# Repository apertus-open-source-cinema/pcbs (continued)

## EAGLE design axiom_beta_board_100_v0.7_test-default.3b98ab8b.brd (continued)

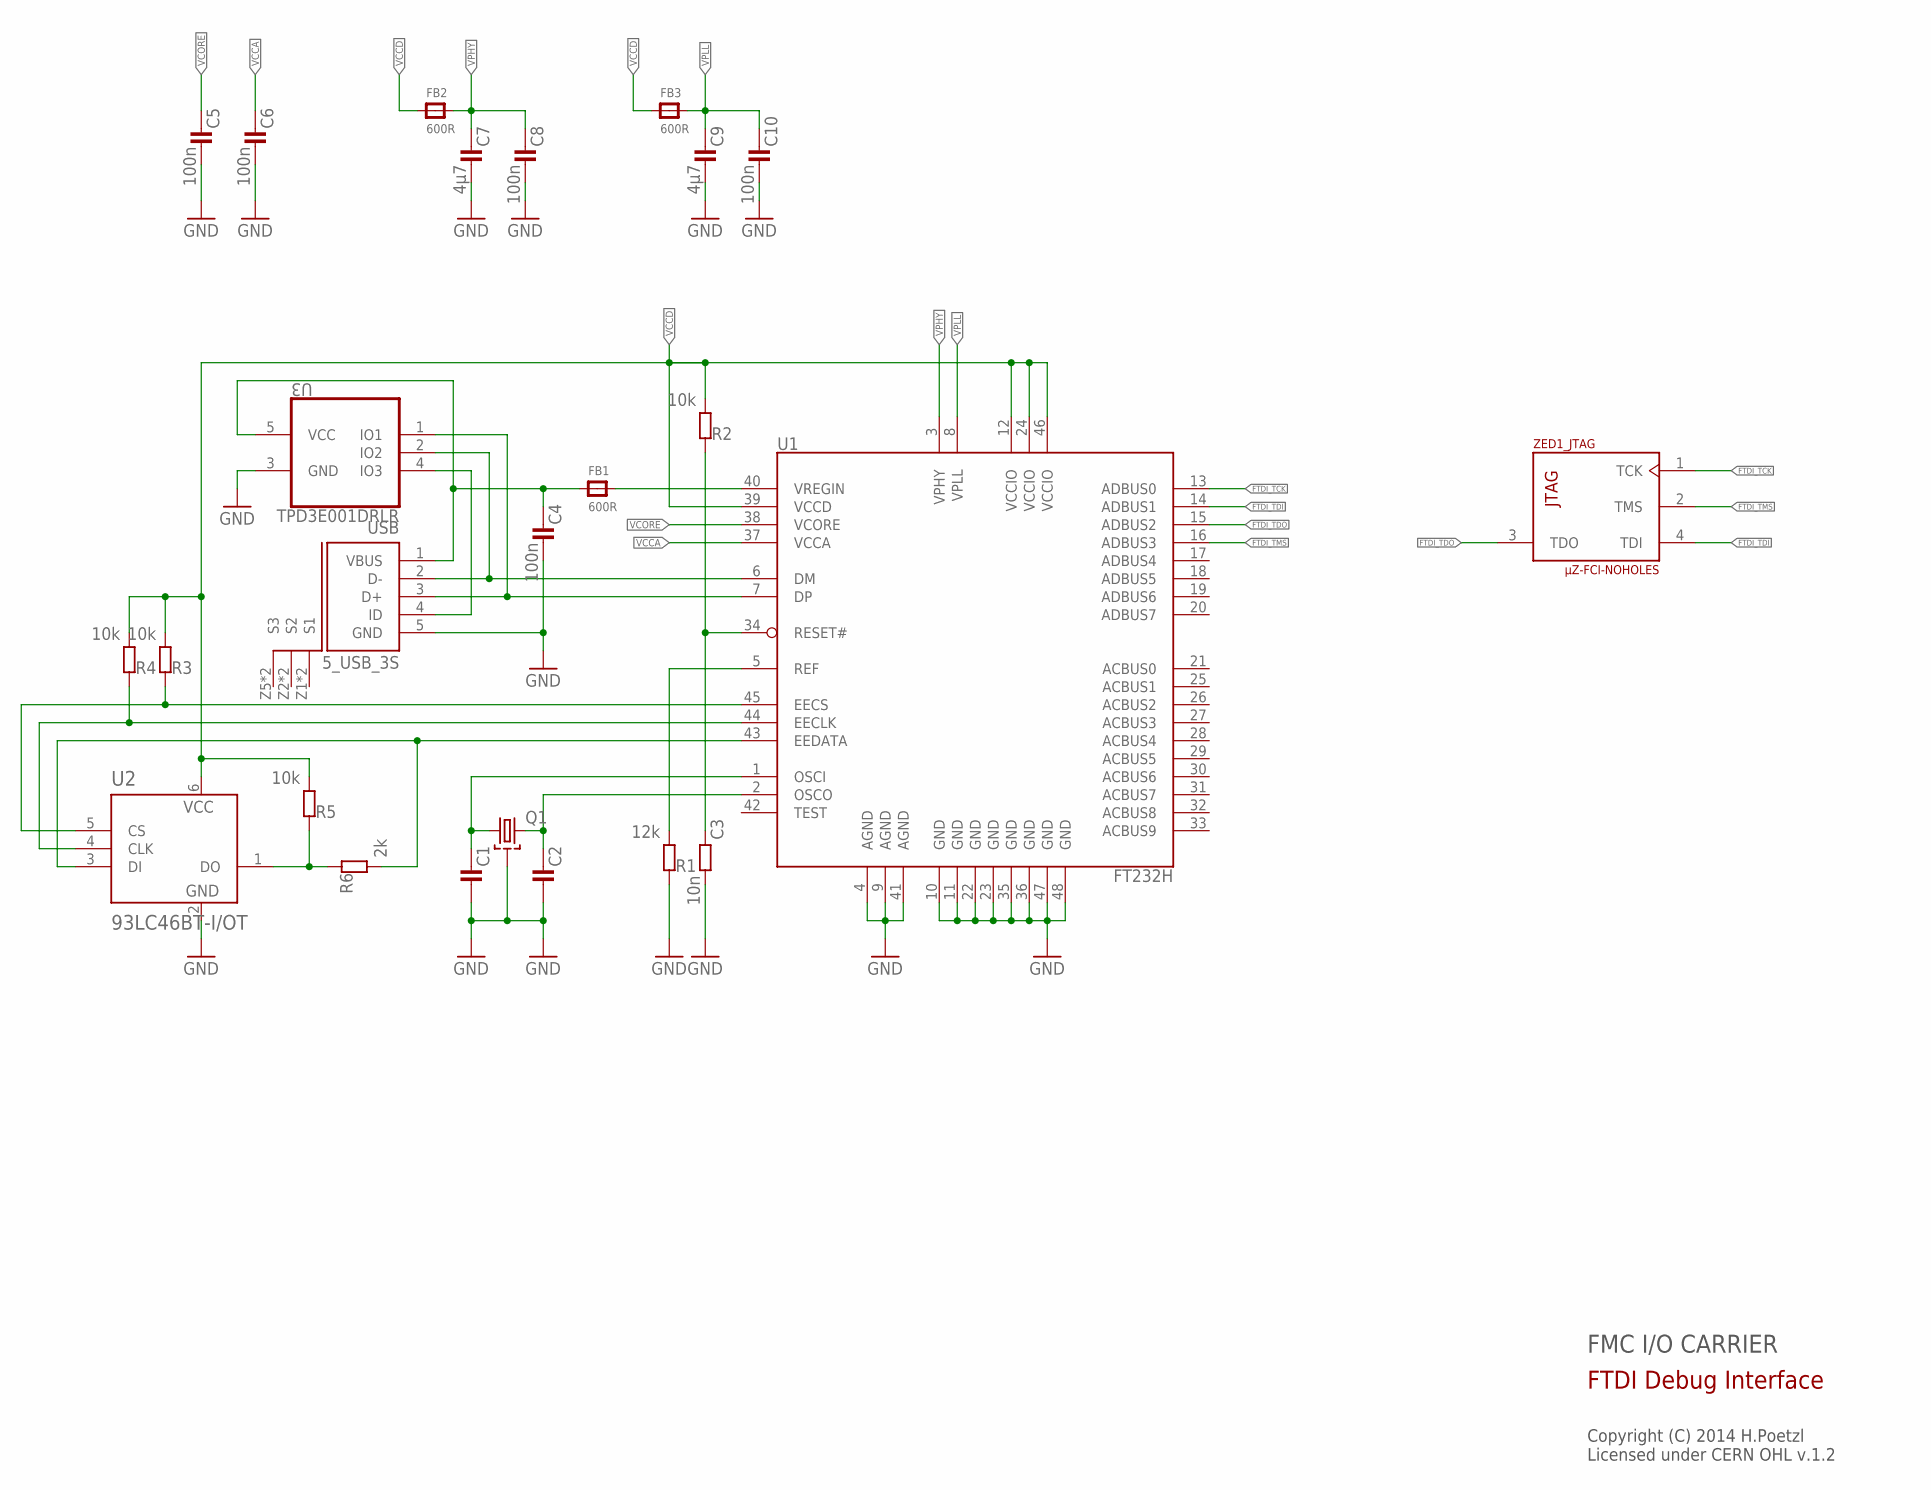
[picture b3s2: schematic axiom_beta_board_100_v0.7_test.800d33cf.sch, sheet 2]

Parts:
C1, C2: C0402-B; 0402-B
C3: 10n; 0402-B
C4: 100n; 0603-B
C5, C6, C8, C10: 100n; 0402-B
C7, C9: 4µ7; 0603-B
FB1, FB2, FB3: 600R; _0603MP
Q1: SMD-4P-2G-3.2X2.5; ABM8G
R1: 12k; 0402-B
R2, R3, R4, R5: 10k; 0402-B
R6: 2k; 0402-B
U1: FT232H; LQFP48
U2: 93LC46BT-I/OT; SOT95P280X145-6N
U3: TPD3E001DRLR; SOT50P160X60-5N
USB: 5_USB_3S; MICRO-AB-H-SMT
ZED1: µZ-FCI-NOHOLES; µZ-NOHOLES

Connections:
EE_CLK1: R4.1, U1.44 (EECLK), U2.4 (CLK)
EE_CS1: R3.1, U1.45 (EECS), U2.5 (CS)
EE_DATA1: R6.2, U1.43 (EEDATA), U2.3 (DI)
FTDI_D_N: U1.6 (DM), U3.2 (IO2), USB.2 (D-)
FTDI_D_P: U1.7 (DP), U3.1 (IO1), USB.3 (D+)
FTDI_TCK: U1.13 (ADBUS0), ZED1.1 (TCK)
FTDI_TDI: U1.14 (ADBUS1), ZED1.4 (TDI)
FTDI_TDO: U1.15 (ADBUS2), ZED1.3 (TDO)
FTDI_TMS: U1.16 (ADBUS3), ZED1.2 (TMS)
unnamed: R5.1, R6.1, U2.1 (DO)
unnamed: C1.1, Q1.1, U1.1 (OSCI)
unnamed: C2.1, Q1.3 (2), U1.2 (OSCO)
unnamed: C3.1, R2.1, U1.34 (RESET#)
unnamed: R1.2, U1.5 (REF)
unnamed: U3.4 (IO3), USB.4 (ID)
VBUS: C4.1, FB1.1, U3.5 (VCC), USB.1 (VBUS)
VCCA: C6.1, U1.37 (VCCA)
VCCD: FB2.1, FB3.1, R2.2, R3.2, R4.2, R5.2, U1.12 (VCCIO), U1.24 (VCCIO), U1.39 (VCCD), U1.46 (VCCIO), U2.6 (VCC)
VCORE: C5.1, U1.38 (VCORE)
VPHY: C7.1, C8.1, FB2.2, U1.3 (VPHY)
VPLL: C9.1, C10.1, FB3.2, U1.8 (VPLL)
VREGIN: FB1.2, U1.40 (VREGIN)

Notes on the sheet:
FMC I/O CARRIER
Copyright (C) 2014 H.Poetzl Licensed under CERN OHL v.1.2
FTDI Debug Interface

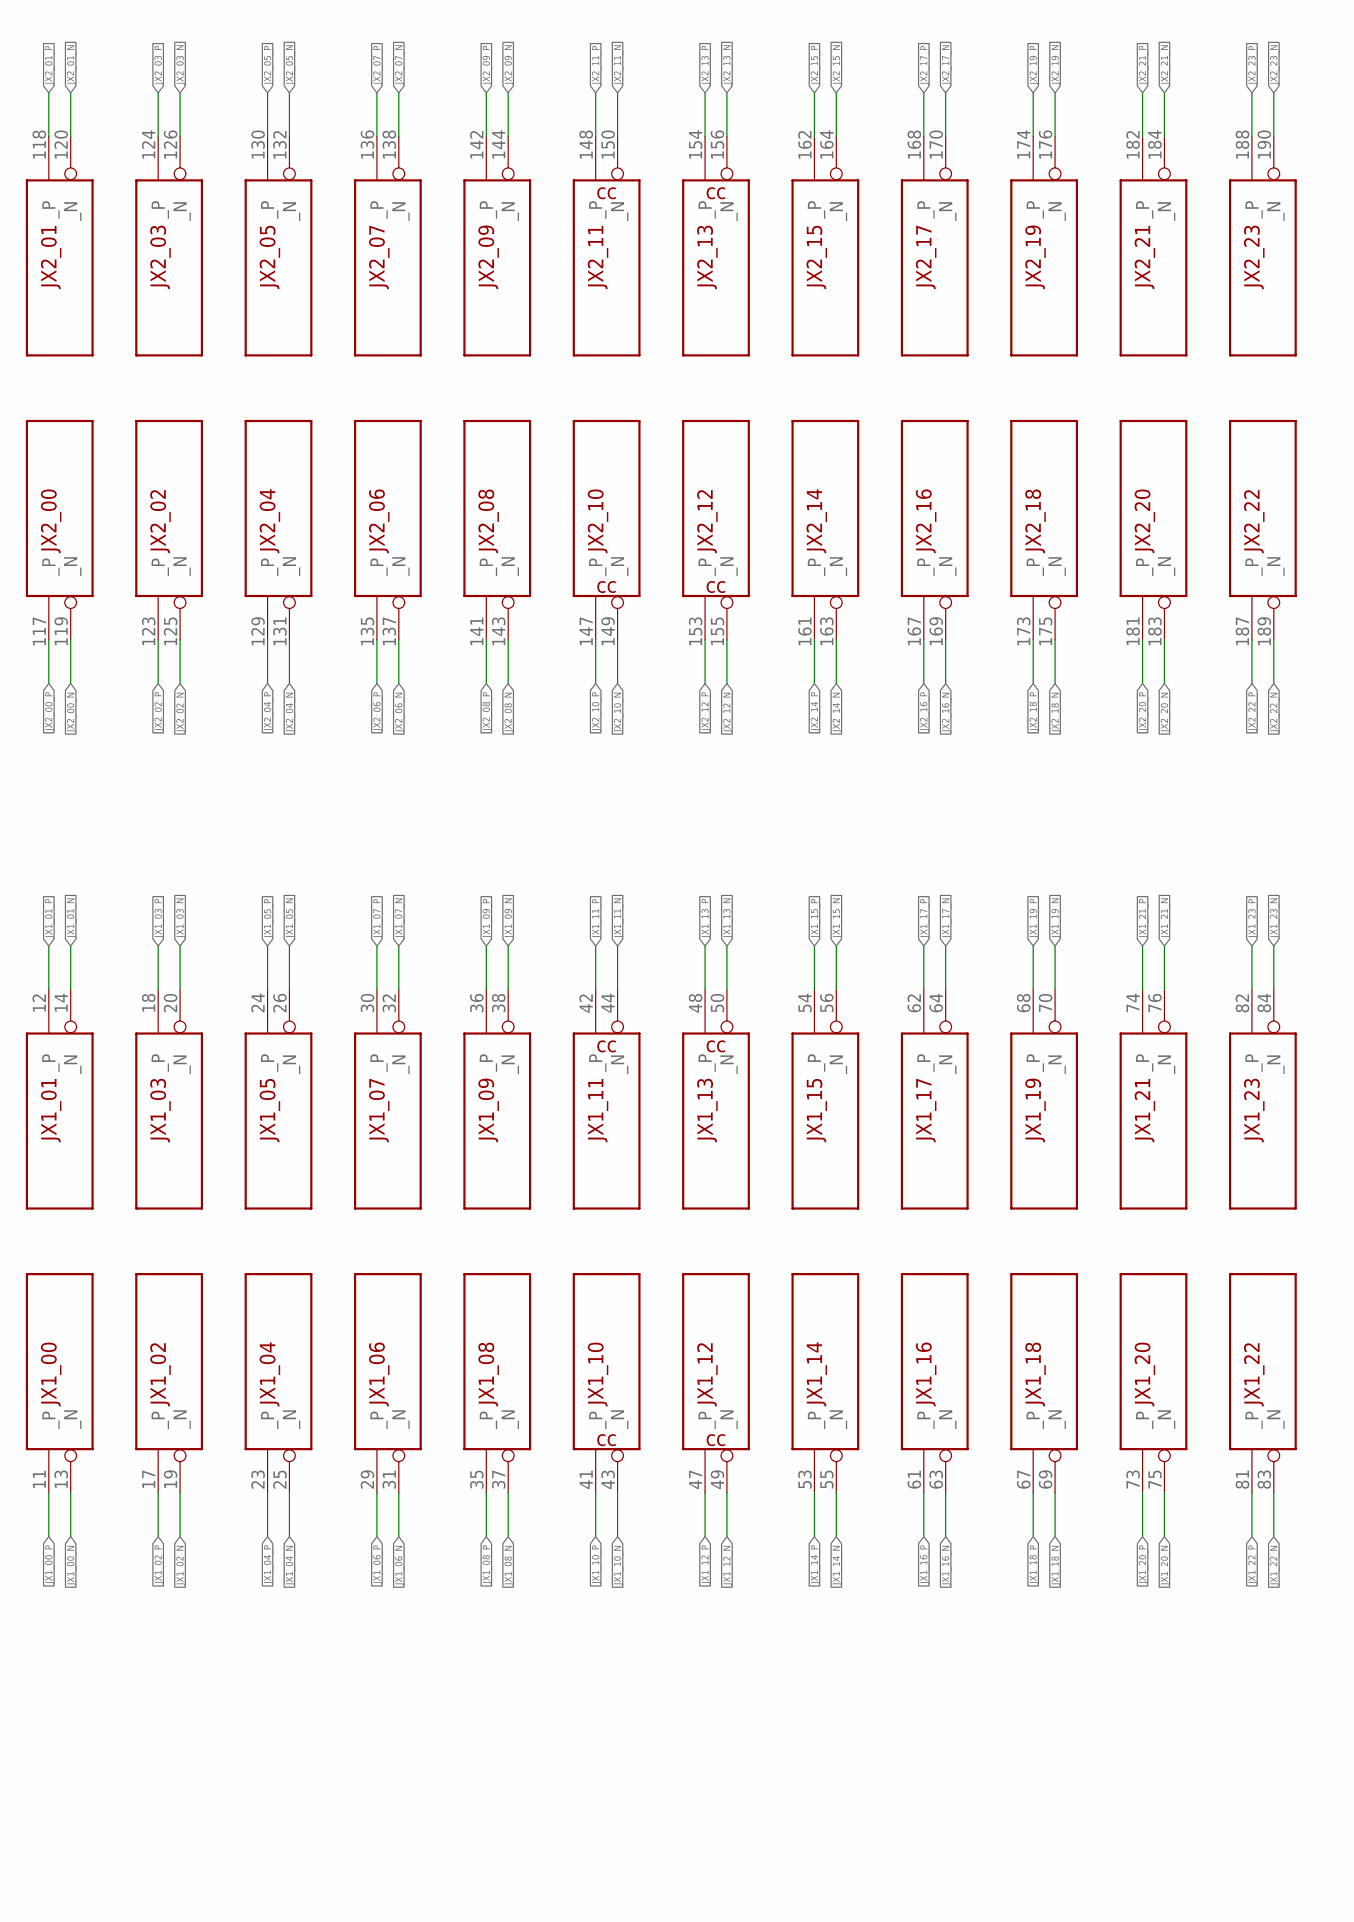
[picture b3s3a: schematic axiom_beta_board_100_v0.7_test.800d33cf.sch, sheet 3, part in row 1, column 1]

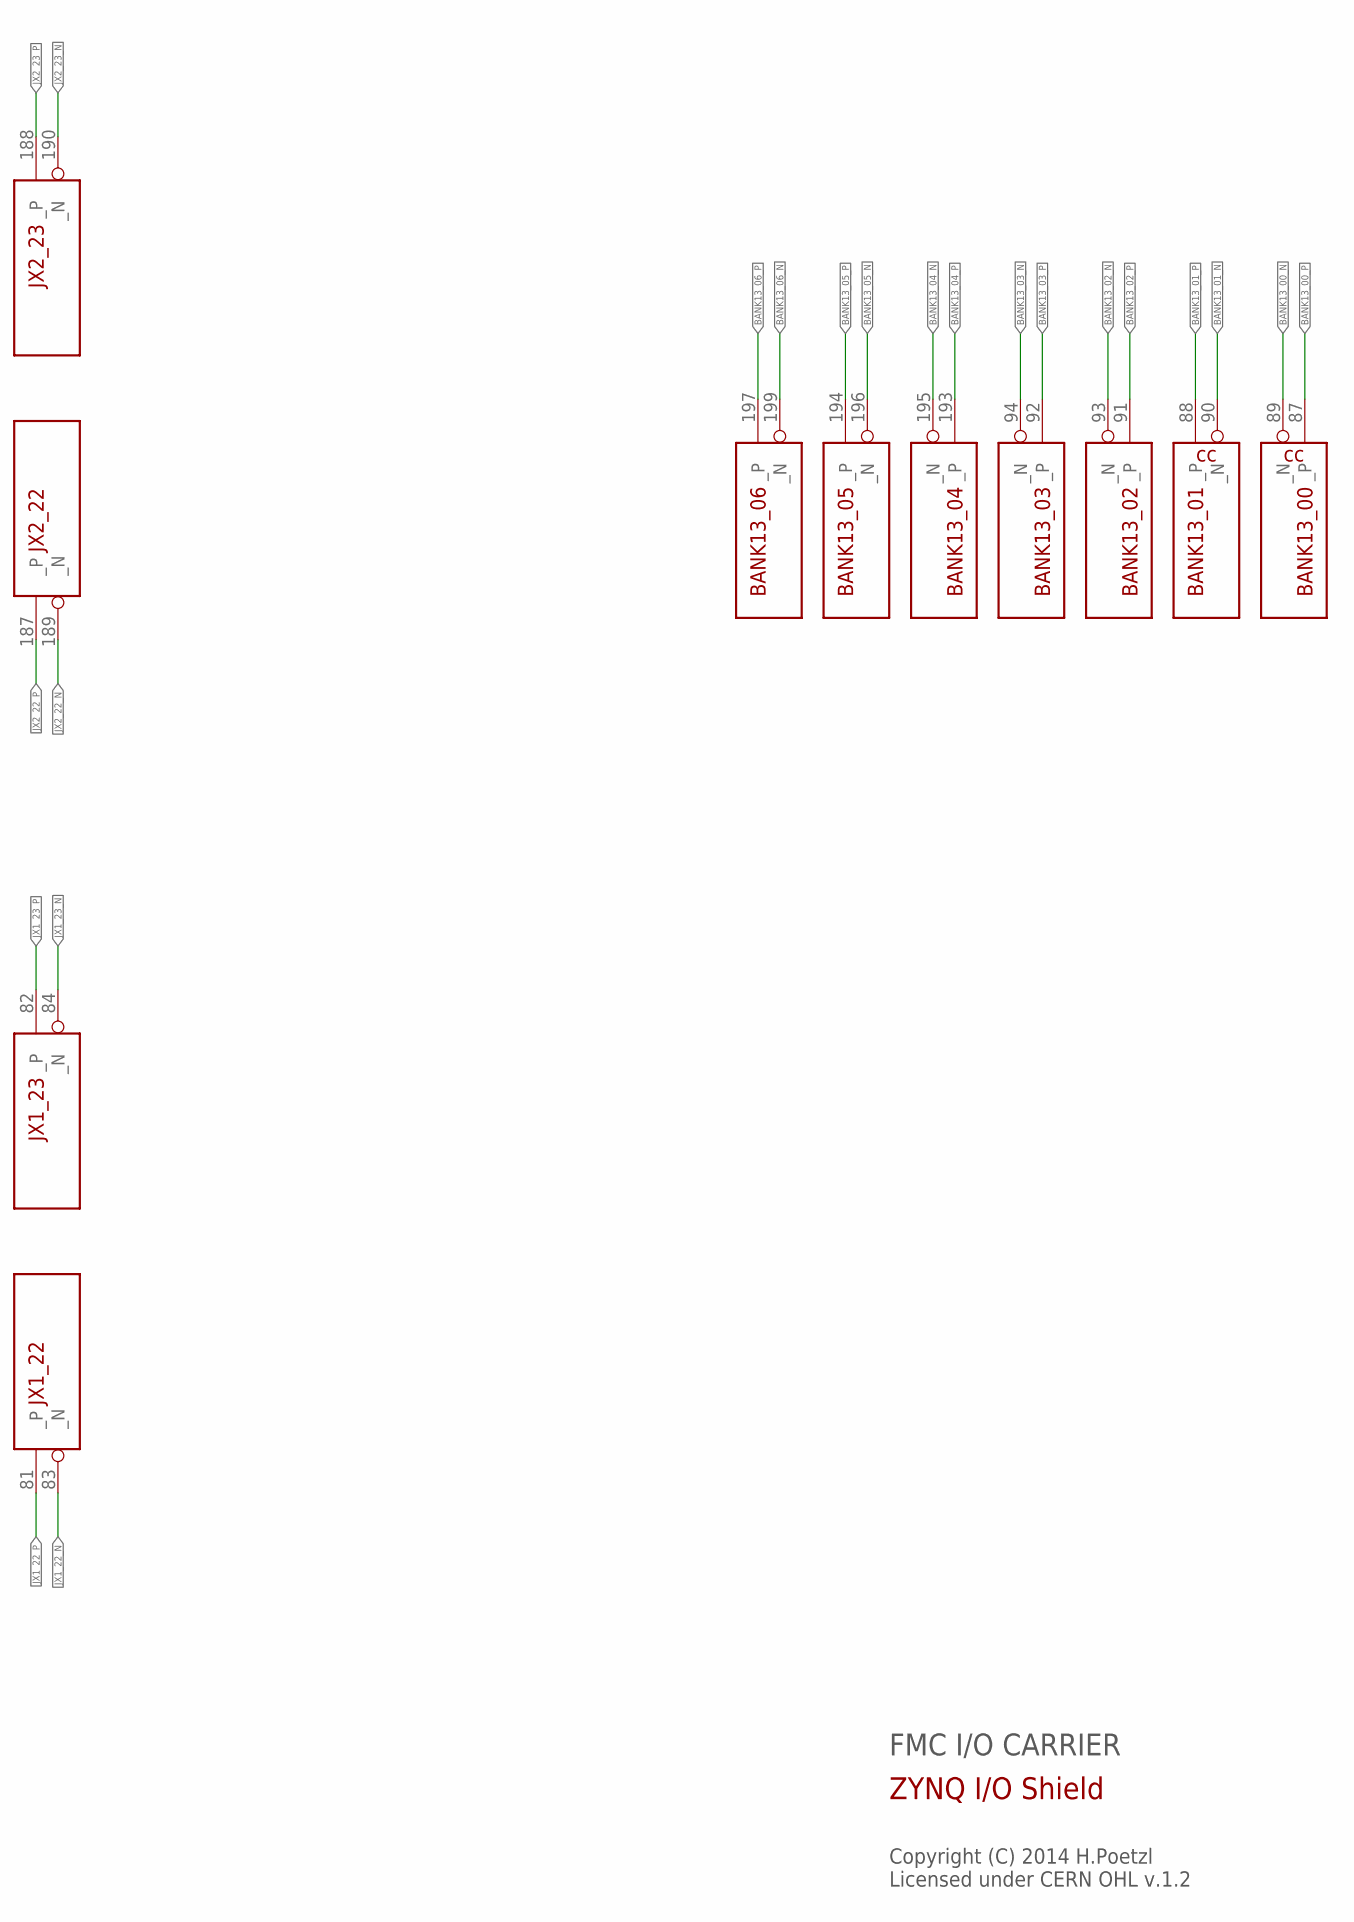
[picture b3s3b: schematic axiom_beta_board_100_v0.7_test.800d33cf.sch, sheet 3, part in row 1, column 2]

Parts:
ZED1: µZ-FCI-NOHOLES; µZ-NOHOLES

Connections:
BANK13_00_N: ZED1.89 (_N); also elsewhere on the board
BANK13_00_P: ZED1.87 (_P); also elsewhere on the board
BANK13_01_N: ZED1.90 (_N); also elsewhere on the board
BANK13_01_P: ZED1.88 (_P); also elsewhere on the board
BANK13_02_N: ZED1.93 (_N); also elsewhere on the board
BANK13_02_P: ZED1.91 (_P); also elsewhere on the board
BANK13_03_N: ZED1.94 (_N)
BANK13_03_P: ZED1.92 (_P)
BANK13_04_N: ZED1.195 (_N); also elsewhere on the board
BANK13_04_P: ZED1.193 (_P); also elsewhere on the board
BANK13_05_N: ZED1.196 (_N); also elsewhere on the board
BANK13_05_P: ZED1.194 (_P); also elsewhere on the board
BANK13_06_N: ZED1.199 (_N); also elsewhere on the board
BANK13_06_P: ZED1.197 (_P); also elsewhere on the board
JX1_00_N: ZED1.13 (_N); also elsewhere on the board
JX1_00_P: ZED1.11 (_P); also elsewhere on the board
JX1_01_N: ZED1.14 (_N); also elsewhere on the board
JX1_01_P: ZED1.12 (_P); also elsewhere on the board
JX1_02_N: ZED1.19 (_N); also elsewhere on the board
JX1_02_P: ZED1.17 (_P); also elsewhere on the board
JX1_03_N: ZED1.20 (_N); also elsewhere on the board
JX1_03_P: ZED1.18 (_P); also elsewhere on the board
JX1_04_N: ZED1.25 (_N); also elsewhere on the board
JX1_04_P: ZED1.23 (_P); also elsewhere on the board
JX1_05_N: ZED1.26 (_N); also elsewhere on the board
JX1_05_P: ZED1.24 (_P); also elsewhere on the board
JX1_06_N: ZED1.31 (_N); also elsewhere on the board
JX1_06_P: ZED1.29 (_P); also elsewhere on the board
JX1_07_N: ZED1.32 (_N); also elsewhere on the board
JX1_07_P: ZED1.30 (_P); also elsewhere on the board
JX1_08_N: ZED1.37 (_N); also elsewhere on the board
JX1_08_P: ZED1.35 (_P); also elsewhere on the board
JX1_09_N: ZED1.38 (_N); also elsewhere on the board
JX1_09_P: ZED1.36 (_P); also elsewhere on the board
JX1_10_N: ZED1.43 (_N); also elsewhere on the board
JX1_10_P: ZED1.41 (_P); also elsewhere on the board
JX1_11_N: ZED1.44 (_N); also elsewhere on the board
JX1_11_P: ZED1.42 (_P); also elsewhere on the board
JX1_12_N: ZED1.49 (_N); also elsewhere on the board
JX1_12_P: ZED1.47 (_P); also elsewhere on the board
JX1_13_N: ZED1.50 (_N); also elsewhere on the board
JX1_13_P: ZED1.48 (_P); also elsewhere on the board
JX1_14_N: ZED1.55 (_N); also elsewhere on the board
JX1_14_P: ZED1.53 (_P); also elsewhere on the board
JX1_15_N: ZED1.56 (_N); also elsewhere on the board
JX1_15_P: ZED1.54 (_P); also elsewhere on the board
JX1_16_N: ZED1.63 (_N); also elsewhere on the board
JX1_16_P: ZED1.61 (_P); also elsewhere on the board
JX1_17_N: ZED1.64 (_N); also elsewhere on the board
JX1_17_P: ZED1.62 (_P); also elsewhere on the board
JX1_18_N: ZED1.69 (_N); also elsewhere on the board
JX1_18_P: ZED1.67 (_P); also elsewhere on the board
JX1_19_N: ZED1.70 (_N); also elsewhere on the board
JX1_19_P: ZED1.68 (_P); also elsewhere on the board
JX1_20_N: ZED1.75 (_N); also elsewhere on the board
JX1_20_P: ZED1.73 (_P); also elsewhere on the board
JX1_21_N: ZED1.76 (_N); also elsewhere on the board
JX1_21_P: ZED1.74 (_P); also elsewhere on the board
JX1_22_N: ZED1.83 (_N); also elsewhere on the board
JX1_22_P: ZED1.81 (_P); also elsewhere on the board
JX1_23_N: ZED1.84 (_N); also elsewhere on the board
JX1_23_P: ZED1.82 (_P); also elsewhere on the board
JX2_00_N: ZED1.119 (_N); also elsewhere on the board
JX2_00_P: ZED1.117 (_P); also elsewhere on the board
JX2_01_N: ZED1.120 (_N); also elsewhere on the board
JX2_01_P: ZED1.118 (_P); also elsewhere on the board
JX2_02_N: ZED1.125 (_N); also elsewhere on the board
JX2_02_P: ZED1.123 (_P); also elsewhere on the board
JX2_03_N: ZED1.126 (_N); also elsewhere on the board
JX2_03_P: ZED1.124 (_P); also elsewhere on the board
JX2_04_N: ZED1.131 (_N); also elsewhere on the board
JX2_04_P: ZED1.129 (_P); also elsewhere on the board
JX2_05_N: ZED1.132 (_N); also elsewhere on the board
JX2_05_P: ZED1.130 (_P); also elsewhere on the board
JX2_06_N: ZED1.137 (_N); also elsewhere on the board
JX2_06_P: ZED1.135 (_P); also elsewhere on the board
JX2_07_N: ZED1.138 (_N); also elsewhere on the board
JX2_07_P: ZED1.136 (_P); also elsewhere on the board
JX2_08_N: ZED1.143 (_N); also elsewhere on the board
JX2_08_P: ZED1.141 (_P); also elsewhere on the board
JX2_09_N: ZED1.144 (_N); also elsewhere on the board
JX2_09_P: ZED1.142 (_P); also elsewhere on the board
JX2_10_N: ZED1.149 (_N); also elsewhere on the board
JX2_10_P: ZED1.147 (_P); also elsewhere on the board
JX2_11_N: ZED1.150 (_N); also elsewhere on the board
JX2_11_P: ZED1.148 (_P); also elsewhere on the board
JX2_12_N: ZED1.155 (_N); also elsewhere on the board
JX2_12_P: ZED1.153 (_P); also elsewhere on the board
JX2_13_N: ZED1.156 (_N); also elsewhere on the board
JX2_13_P: ZED1.154 (_P); also elsewhere on the board
JX2_14_N: ZED1.163 (_N); also elsewhere on the board
JX2_14_P: ZED1.161 (_P); also elsewhere on the board
JX2_15_N: ZED1.164 (_N); also elsewhere on the board
JX2_15_P: ZED1.162 (_P); also elsewhere on the board
JX2_16_N: ZED1.169 (_N); also elsewhere on the board
JX2_16_P: ZED1.167 (_P); also elsewhere on the board
JX2_17_N: ZED1.170 (_N); also elsewhere on the board
JX2_17_P: ZED1.168 (_P); also elsewhere on the board
JX2_18_N: ZED1.175 (_N); also elsewhere on the board
JX2_18_P: ZED1.173 (_P); also elsewhere on the board
JX2_19_N: ZED1.176 (_N); also elsewhere on the board
JX2_19_P: ZED1.174 (_P); also elsewhere on the board
JX2_20_N: ZED1.183 (_N); also elsewhere on the board
JX2_20_P: ZED1.181 (_P); also elsewhere on the board
JX2_21_N: ZED1.184 (_N); also elsewhere on the board
JX2_21_P: ZED1.182 (_P); also elsewhere on the board
JX2_22_N: ZED1.189 (_N); also elsewhere on the board
JX2_22_P: ZED1.187 (_P); also elsewhere on the board
JX2_23_N: ZED1.190 (_N); also elsewhere on the board
JX2_23_P: ZED1.188 (_P); also elsewhere on the board

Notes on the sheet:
FMC I/O CARRIER
Copyright (C) 2014 H.Poetzl Licensed under CERN OHL v.1.2
ZYNQ I/O Shield

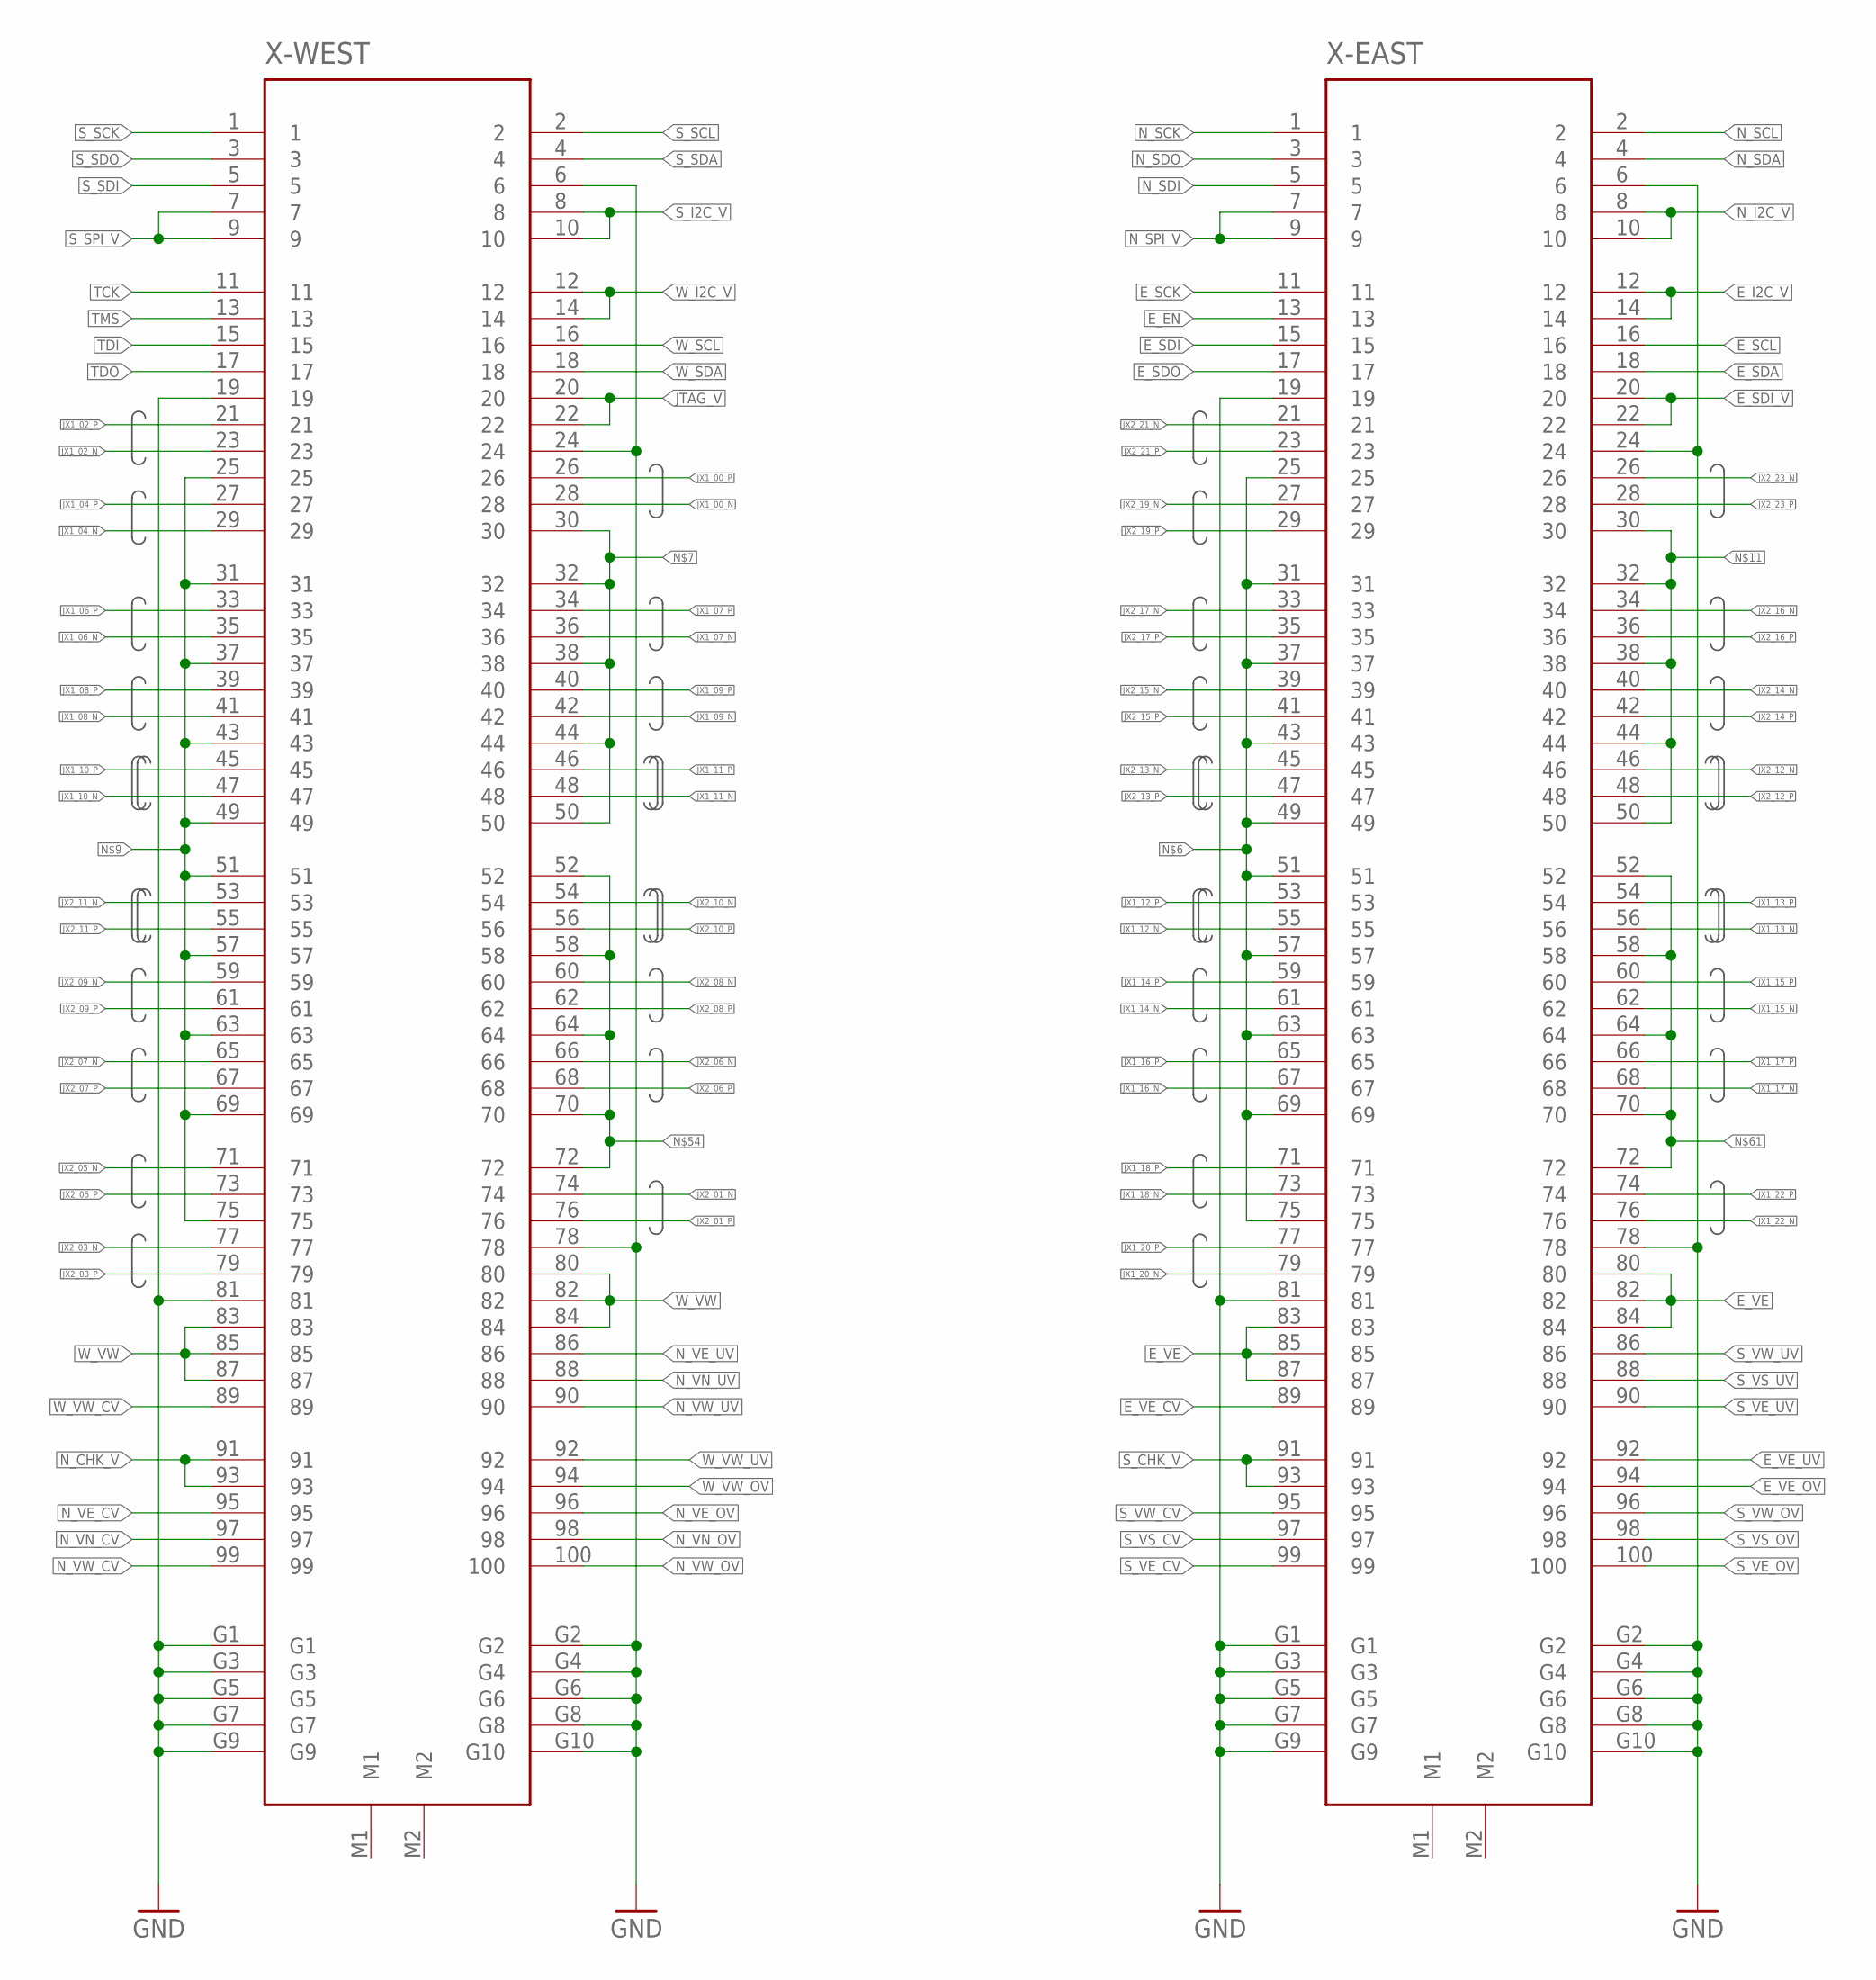
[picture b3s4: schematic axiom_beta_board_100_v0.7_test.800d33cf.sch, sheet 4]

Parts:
X-EAST: FX10-100/10S; FX10A-100S/10
X-WEST: FX10-100/10S; FX10A-100S/10

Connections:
E_EN: X-EAST.13; also elsewhere on the board
E_I2C_V: X-EAST.12, X-EAST.14; also elsewhere on the board
E_SCK: X-EAST.11; also elsewhere on the board
E_SCL: X-EAST.16; also elsewhere on the board
E_SDA: X-EAST.18; also elsewhere on the board
E_SDI: X-EAST.15; also elsewhere on the board
E_SDI_V: X-EAST.20, X-EAST.22; also elsewhere on the board
E_SDO: X-EAST.17; also elsewhere on the board
E_VE: X-EAST.80, X-EAST.82, X-EAST.83, X-EAST.84, X-EAST.85, X-EAST.87; also elsewhere on the board
E_VE_CV: X-EAST.89; also elsewhere on the board
E_VE_OV: X-EAST.94; also elsewhere on the board
E_VE_UV: X-EAST.92; also elsewhere on the board
JTAG_V: X-WEST.20, X-WEST.22; also elsewhere on the board
JX1_00_N: X-WEST.28; also elsewhere on the board
JX1_00_P: X-WEST.26; also elsewhere on the board
JX1_02_N: X-WEST.23; also elsewhere on the board
JX1_02_P: X-WEST.21; also elsewhere on the board
JX1_04_N: X-WEST.29; also elsewhere on the board
JX1_04_P: X-WEST.27; also elsewhere on the board
JX1_06_N: X-WEST.35; also elsewhere on the board
JX1_06_P: X-WEST.33; also elsewhere on the board
JX1_07_N: X-WEST.36; also elsewhere on the board
JX1_07_P: X-WEST.34; also elsewhere on the board
JX1_08_N: X-WEST.41; also elsewhere on the board
JX1_08_P: X-WEST.39; also elsewhere on the board
JX1_09_N: X-WEST.42; also elsewhere on the board
JX1_09_P: X-WEST.40; also elsewhere on the board
JX1_10_N: X-WEST.47; also elsewhere on the board
JX1_10_P: X-WEST.45; also elsewhere on the board
JX1_11_N: X-WEST.48; also elsewhere on the board
JX1_11_P: X-WEST.46; also elsewhere on the board
JX1_12_N: X-EAST.55; also elsewhere on the board
JX1_12_P: X-EAST.53; also elsewhere on the board
JX1_13_N: X-EAST.56; also elsewhere on the board
JX1_13_P: X-EAST.54; also elsewhere on the board
JX1_14_N: X-EAST.61; also elsewhere on the board
JX1_14_P: X-EAST.59; also elsewhere on the board
JX1_15_N: X-EAST.62; also elsewhere on the board
JX1_15_P: X-EAST.60; also elsewhere on the board
JX1_16_N: X-EAST.67; also elsewhere on the board
JX1_16_P: X-EAST.65; also elsewhere on the board
JX1_17_N: X-EAST.68; also elsewhere on the board
JX1_17_P: X-EAST.66; also elsewhere on the board
JX1_18_N: X-EAST.73; also elsewhere on the board
JX1_18_P: X-EAST.71; also elsewhere on the board
JX1_20_N: X-EAST.79; also elsewhere on the board
JX1_20_P: X-EAST.77; also elsewhere on the board
JX1_22_N: X-EAST.76; also elsewhere on the board
JX1_22_P: X-EAST.74; also elsewhere on the board
JX2_01_N: X-WEST.74; also elsewhere on the board
JX2_01_P: X-WEST.76; also elsewhere on the board
JX2_03_N: X-WEST.77; also elsewhere on the board
JX2_03_P: X-WEST.79; also elsewhere on the board
JX2_05_N: X-WEST.71; also elsewhere on the board
JX2_05_P: X-WEST.73; also elsewhere on the board
JX2_06_N: X-WEST.66; also elsewhere on the board
JX2_06_P: X-WEST.68; also elsewhere on the board
JX2_07_N: X-WEST.65; also elsewhere on the board
JX2_07_P: X-WEST.67; also elsewhere on the board
JX2_08_N: X-WEST.60; also elsewhere on the board
JX2_08_P: X-WEST.62; also elsewhere on the board
JX2_09_N: X-WEST.59; also elsewhere on the board
JX2_09_P: X-WEST.61; also elsewhere on the board
JX2_10_N: X-WEST.54; also elsewhere on the board
JX2_10_P: X-WEST.56; also elsewhere on the board
JX2_11_N: X-WEST.53; also elsewhere on the board
JX2_11_P: X-WEST.55; also elsewhere on the board
JX2_12_N: X-EAST.46; also elsewhere on the board
JX2_12_P: X-EAST.48; also elsewhere on the board
JX2_13_N: X-EAST.45; also elsewhere on the board
JX2_13_P: X-EAST.47; also elsewhere on the board
JX2_14_N: X-EAST.40; also elsewhere on the board
JX2_14_P: X-EAST.42; also elsewhere on the board
JX2_15_N: X-EAST.39; also elsewhere on the board
JX2_15_P: X-EAST.41; also elsewhere on the board
JX2_16_N: X-EAST.34; also elsewhere on the board
JX2_16_P: X-EAST.36; also elsewhere on the board
JX2_17_N: X-EAST.33; also elsewhere on the board
JX2_17_P: X-EAST.35; also elsewhere on the board
JX2_19_N: X-EAST.27; also elsewhere on the board
JX2_19_P: X-EAST.29; also elsewhere on the board
JX2_21_N: X-EAST.21; also elsewhere on the board
JX2_21_P: X-EAST.23; also elsewhere on the board
JX2_23_N: X-EAST.26; also elsewhere on the board
JX2_23_P: X-EAST.28; also elsewhere on the board
N_CHK_V: X-WEST.91, X-WEST.93; also elsewhere on the board
N_I2C_V: X-EAST.8, X-EAST.10; also elsewhere on the board
N_SCK: X-EAST.1; also elsewhere on the board
N_SCL: X-EAST.2; also elsewhere on the board
N_SDA: X-EAST.4; also elsewhere on the board
N_SDI: X-EAST.5; also elsewhere on the board
N_SDO: X-EAST.3; also elsewhere on the board
N_SPI_V: X-EAST.7, X-EAST.9; also elsewhere on the board
N_VE_CV: X-WEST.95; also elsewhere on the board
N_VE_OV: X-WEST.96; also elsewhere on the board
N_VE_UV: X-WEST.86; also elsewhere on the board
N_VN_CV: X-WEST.97; also elsewhere on the board
N_VN_OV: X-WEST.98; also elsewhere on the board
N_VN_UV: X-WEST.88; also elsewhere on the board
N_VW_CV: X-WEST.99; also elsewhere on the board
N_VW_OV: X-WEST.100; also elsewhere on the board
N_VW_UV: X-WEST.90; also elsewhere on the board
S_CHK_V: X-EAST.91, X-EAST.93; also elsewhere on the board
S_I2C_V: X-WEST.8, X-WEST.10; also elsewhere on the board
S_SCK: X-WEST.1; also elsewhere on the board
S_SCL: X-WEST.2; also elsewhere on the board
S_SDA: X-WEST.4; also elsewhere on the board
S_SDI: X-WEST.5; also elsewhere on the board
S_SDO: X-WEST.3; also elsewhere on the board
S_SPI_V: X-WEST.7, X-WEST.9; also elsewhere on the board
S_VE_CV: X-EAST.99; also elsewhere on the board
S_VE_OV: X-EAST.100; also elsewhere on the board
S_VE_UV: X-EAST.90; also elsewhere on the board
S_VS_CV: X-EAST.97; also elsewhere on the board
S_VS_OV: X-EAST.98; also elsewhere on the board
S_VS_UV: X-EAST.88; also elsewhere on the board
S_VW_CV: X-EAST.95; also elsewhere on the board
S_VW_OV: X-EAST.96; also elsewhere on the board
S_VW_UV: X-EAST.86; also elsewhere on the board
TCK: X-WEST.11; also elsewhere on the board
TDI: X-WEST.15; also elsewhere on the board
TDO: X-WEST.17; also elsewhere on the board
TMS: X-WEST.13; also elsewhere on the board
W_I2C_V: X-WEST.12, X-WEST.14; also elsewhere on the board
W_SCL: X-WEST.16; also elsewhere on the board
W_SDA: X-WEST.18; also elsewhere on the board
W_VW: X-WEST.80, X-WEST.82, X-WEST.83, X-WEST.84, X-WEST.85, X-WEST.87; also elsewhere on the board
W_VW_CV: X-WEST.89; also elsewhere on the board
W_VW_OV: X-WEST.94; also elsewhere on the board
W_VW_UV: X-WEST.92; also elsewhere on the board
